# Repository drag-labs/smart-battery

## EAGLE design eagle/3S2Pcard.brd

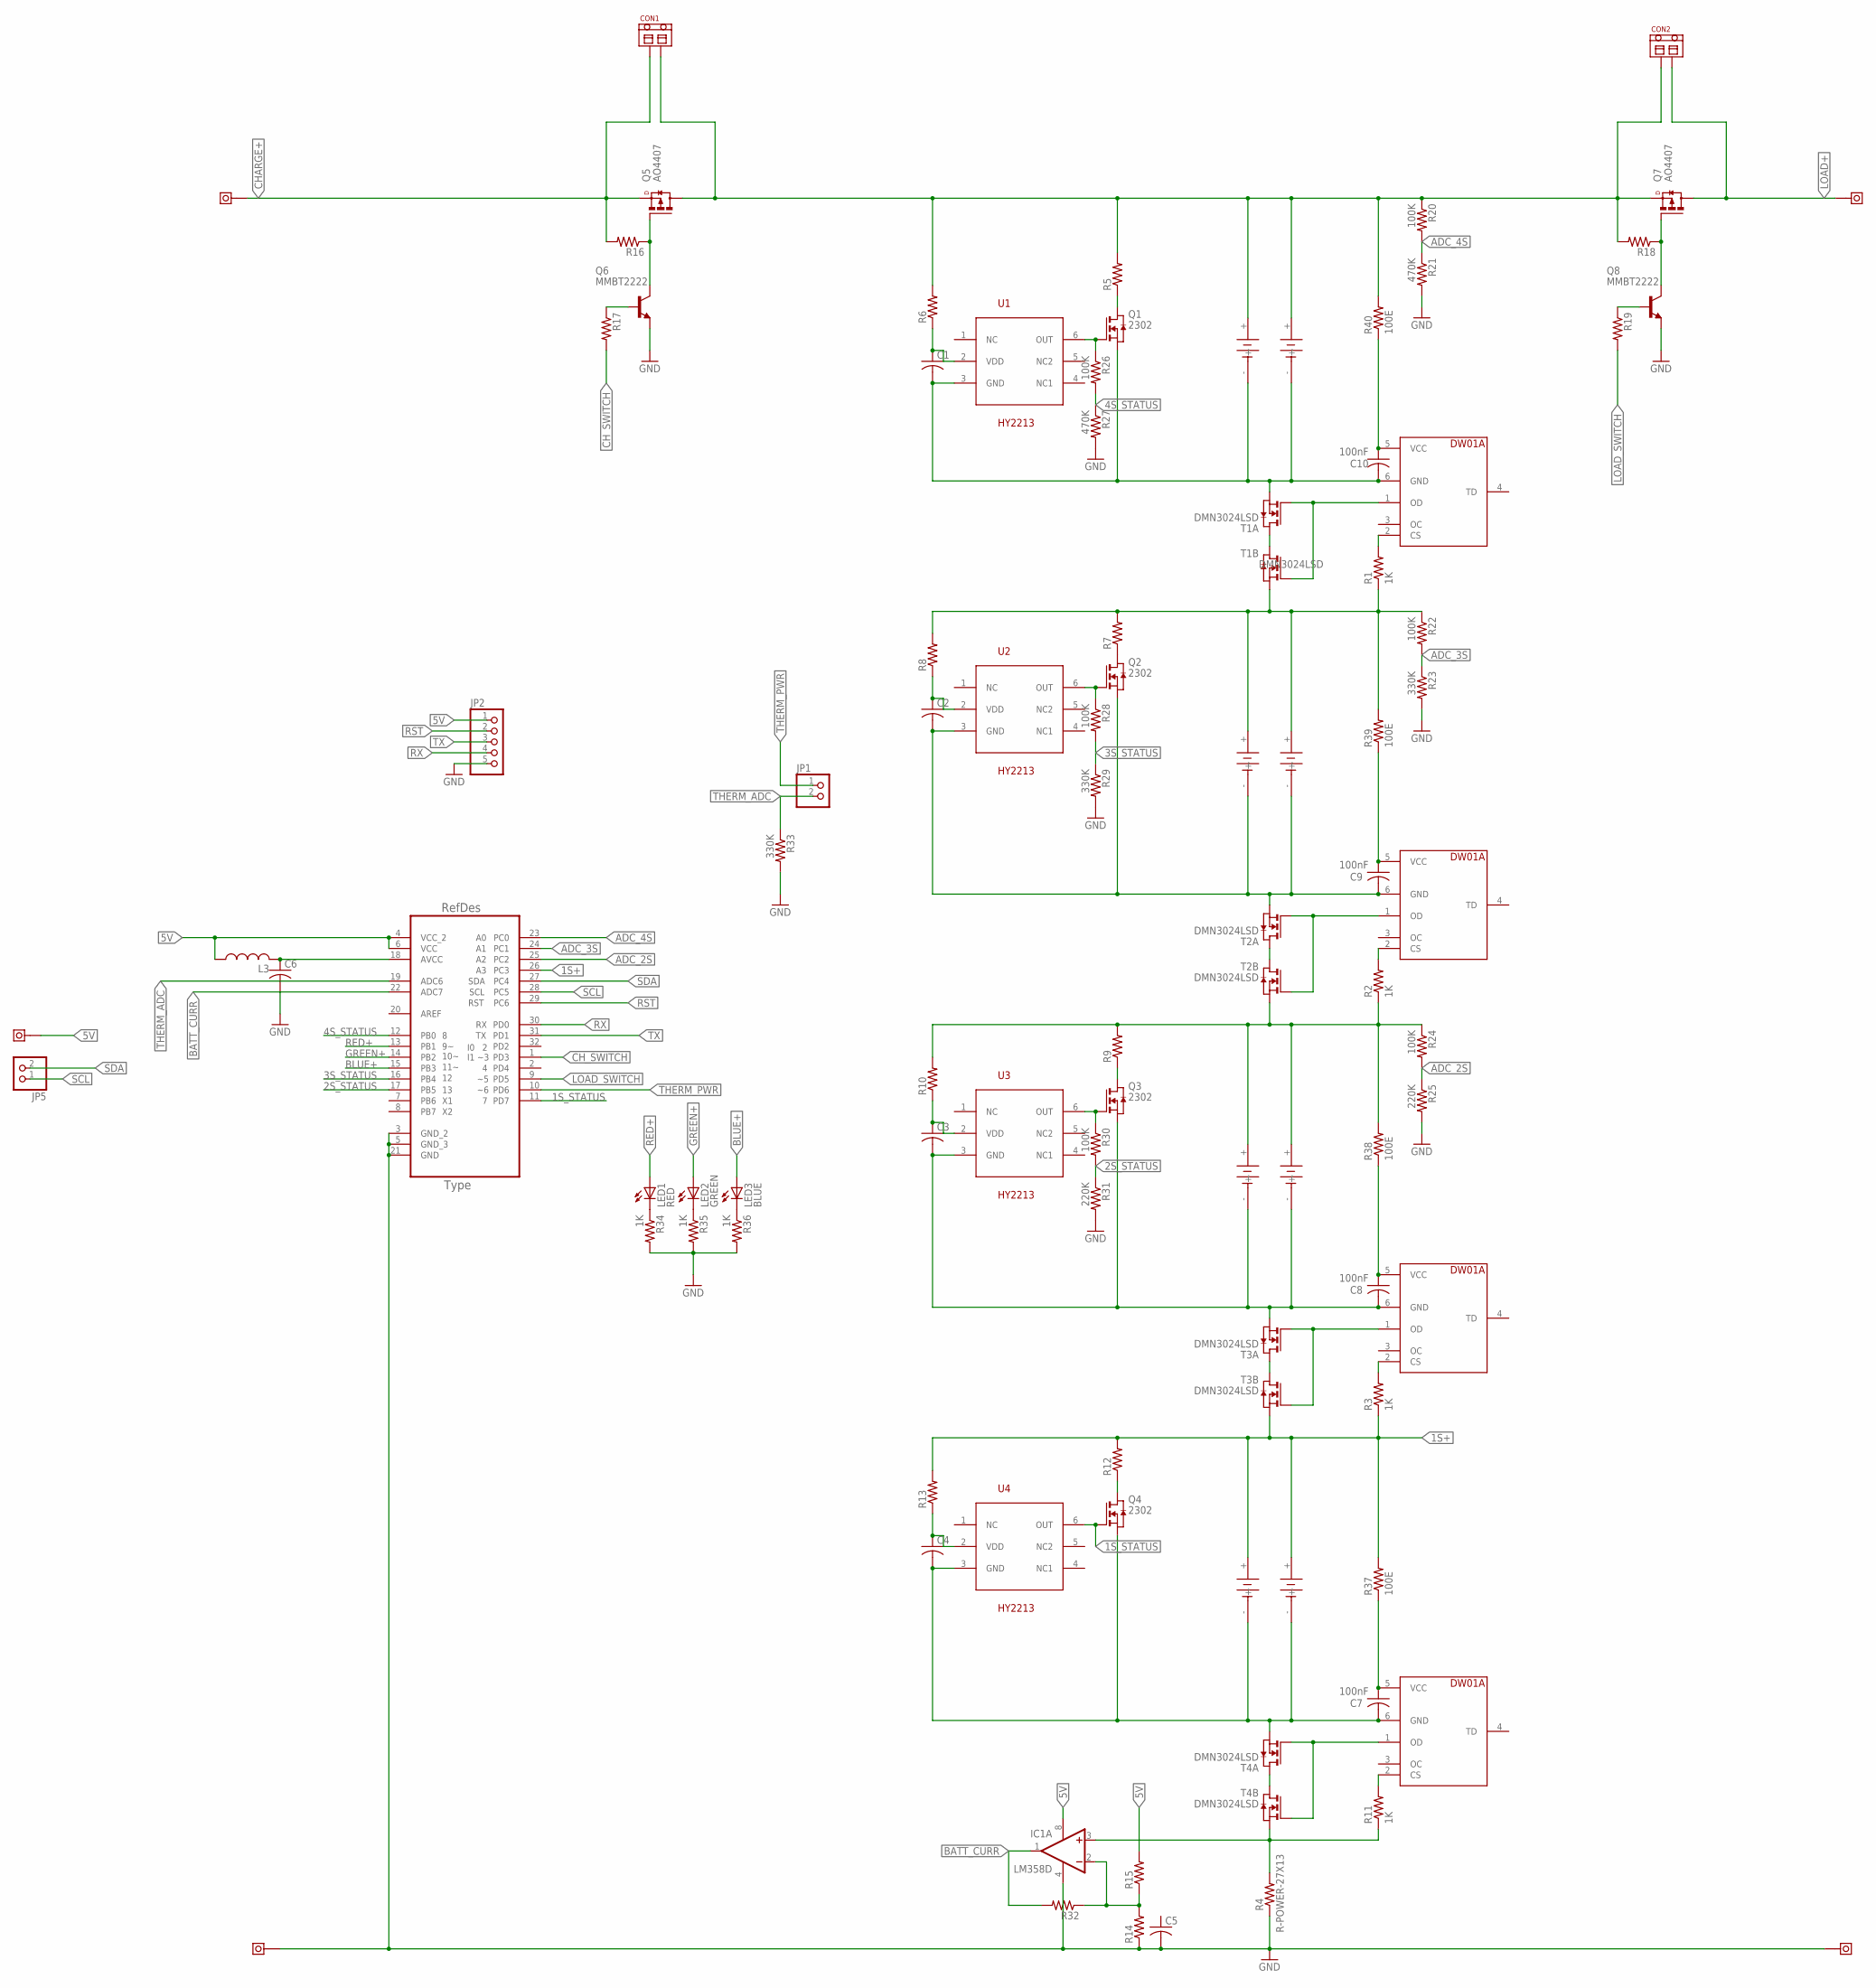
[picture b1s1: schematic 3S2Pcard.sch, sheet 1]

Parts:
B11, B12, B21, B22, B31, B32, B41, B42: 18650_HOLDER
C1, C2, C3, C4, C5, C6: C-USC0805; C0805
C7, C8, C9, C10: 100nF; C0805
CON1, CON2: TERMINAL-SMALL
IC1: LM358D; SO08
JP1, JP5: PINHD-1X2; 1X02
JP2: PINHD-1X5; 1X05
L3: L-US0207/10; 0207/10
LED1: RED; CHIP-LED0805
LED2: GREEN; CHIP-LED0805
LED3: BLUE; CHIP-LED0805
Q1, Q2, Q3, Q4: 2302; TO236
Q5, Q7: AO4407; SOIC8
Q6, Q8: MMBT2222; SOT-23-CBE
R1, R2, R3, R11, R34, R35, R36: 1K; R0805
R4: R-POWER-27X13; R-27X13
R5, R7, R9, R12: R-US_R1206W; R1206W
R6, R8, R10, R13, R14, R15, R16, R17, R18, R19, R32: R-US_R0805; R0805
R20, R22, R24, R26, R28, R30: 100K; R0805
R21, R27: 470K; R0805
R23, R29, R33: 330K; R0805
R25, R31: 220K; R0805
R37, R38, R39, R40: 100E; R0805
T1, T2, T3, T4: DMN3024LSD; TSSOP-8
U1, U2, U3, U4: HY2213; SOT23-6
U5: ATMEGA328P-AU; QFP80P900X900X120-32N
U12: DW01A; SOT23-6
U$7, U$8, U$9: DW01A; SOT23-6
U$13, U$14, U$15, U$16, U$17: METAL_SPACER; SPACER

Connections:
1S+: B11.+, B12.+, R3.1, R12.2, R13.2, R37.2, T3.6 (S), T3.7 (S), U5.26 (PC3)
1S-: B11.-, B12.-, C4.2, C7.2, Q4.3 (S), T4.2 (S), T4.3 (S), U4.3 (GND), U12.6 (GND)
1S_STATUS: Q4.2 (G), U4.6 (OUT), U5.11 (PD7)
2S+: B21.+, B22.+, R2.1, R9.2, R10.2, R24.1, R38.2, T2.6 (S), T2.7 (S)
2S-: B21.-, B22.-, C3.2, C8.2, Q3.3 (S), T3.2 (S), T3.3 (S), U3.3 (GND), U$9.6 (GND)
2S_STATUS: R30.2, R31.1, U5.17 (PB5)
3S+: B31.+, B32.+, R1.1, R7.2, R8.2, R22.1, R39.2, T1.6 (S), T1.7 (S)
3S-: B31.-, B32.-, C2.2, C9.2, Q2.3 (S), T2.2 (S), T2.3 (S), U2.3 (GND), U$8.6 (GND)
3S_STATUS: R28.2, R29.1, U5.16 (PB4)
4S+: B41.+, B42.+, CON1.2, CON2.1, Q5.1 (S), Q5.2 (S), Q5.3 (S), Q7.5 (D), Q7.6 (D), Q7.7 (D), Q7.8 (D), R5.2, R6.2, R18.2, R20.1, R40.2
4S-: B41.-, B42.-, C1.2, C10.2, Q1.3 (S), T1.2 (S), T1.3 (S), U1.3 (GND), U$7.6 (GND)
4S_STATUS: R26.2, R27.1, U5.12 (PB0)
5V: IC1.8 (V+), JP2.1, L3.1, R15.2, U5.4 (VCC_2), U5.6 (VCC), U$17.1
ADC_2S: R24.2, R25.1, U5.25 (PC2)
ADC_3S: R22.2, R23.1, U5.24 (PC1)
ADC_4S: R20.2, R21.1, U5.23 (PC0)
AVCC: C6.1, L3.2, U5.18 (AVCC)
BATT_CURR: IC1.1 (OUT), R32.2, U5.22 (ADC7)
BLUE+: LED3.A, U5.15 (PB3)
CHARGE+: CON1.1, Q5.5 (D), Q5.6 (D), Q5.7 (D), Q5.8 (D), R16.2, U$15.1
CH_SWITCH: R17.2, U5.1 (PD3)
GND: C5.2, C6.2, IC1.4 (V-), JP2.5, Q6.E, Q8.E, R4.1, R14.1, R21.2, R23.2, R25.2, R27.2, R29.2, R31.2, R33.2, R34.2, R35.2, R36.2, U5.3 (GND_2), U5.5 (GND_3), U5.21 (GND), U$14.1, U$16.1
GREEN+: LED2.A, U5.14 (PB2)
LOAD+: CON2.2, Q7.1 (S), Q7.2 (S), Q7.3 (S), U$13.1
LOAD_SWITCH: R19.2, U5.9 (PD5)
unnamed: C7.1, R37.1, U12.5 (VCC)
unnamed: T1.1 (D), T1.8 (D)
unnamed: C8.1, R38.1, U$9.5 (VCC)
unnamed: IC1.2 (-IN), R14.2, R15.1, R32.1
unnamed: T2.1 (D), T2.8 (D)
unnamed: C9.1, R39.1, U$8.5 (VCC)
unnamed: C10.1, R40.1, U$7.5 (VCC)
unnamed: R1.2, U$7.2 (CS)
unnamed: T1.4 (G), T1.5 (G), U$7.1 (OD)
unnamed: R2.2, U$8.2 (CS)
unnamed: T3.1 (D), T3.8 (D)
unnamed: T2.4 (G), T2.5 (G), U$8.1 (OD)
unnamed: LED1.C, R34.1
unnamed: LED2.C, R35.1
unnamed: T3.4 (G), T3.5 (G), U$9.1 (OD)
unnamed: R3.2, U$9.2 (CS)
unnamed: LED3.C, R36.1
unnamed: C1.1, R6.1, U1.2 (VDD)
unnamed: Q1.2 (G), R26.1, U1.6 (OUT)
unnamed: Q1.1 (D), R5.1
unnamed: C2.1, R8.1, U2.2 (VDD)
unnamed: Q2.2 (G), R28.1, U2.6 (OUT)
unnamed: Q2.1 (D), R7.1
unnamed: C3.1, R10.1, U3.2 (VDD)
unnamed: Q3.2 (G), R30.1, U3.6 (OUT)
unnamed: Q3.1 (D), R9.1
unnamed: T4.1 (D), T4.8 (D)
unnamed: T4.4 (G), T4.5 (G), U12.1 (OD)
unnamed: R11.2, U12.2 (CS)
unnamed: C4.1, R13.1, U4.2 (VDD)
unnamed: Q4.1 (D), R12.1
unnamed: IC1.3 (+IN), R4.2, R11.1, T4.6 (S), T4.7 (S)
unnamed: Q5.4 (G), Q6.C, R16.1
unnamed: Q6.B, R17.1
unnamed: Q7.4 (G), Q8.C, R18.1
unnamed: Q8.B, R19.1
RED+: LED1.A, U5.13 (PB1)
RST: JP2.2, U5.29 (PC6)
RX: JP2.4, U5.30 (PD0)
SCL: JP5.1, U5.28 (PC5)
SDA: JP5.2, U5.27 (PC4)
THERM_ADC: JP1.2, R33.1, U5.19 (ADC6)
THERM_PWR: JP1.1, U5.10 (PD6)
TX: JP2.3, U5.31 (PD1)

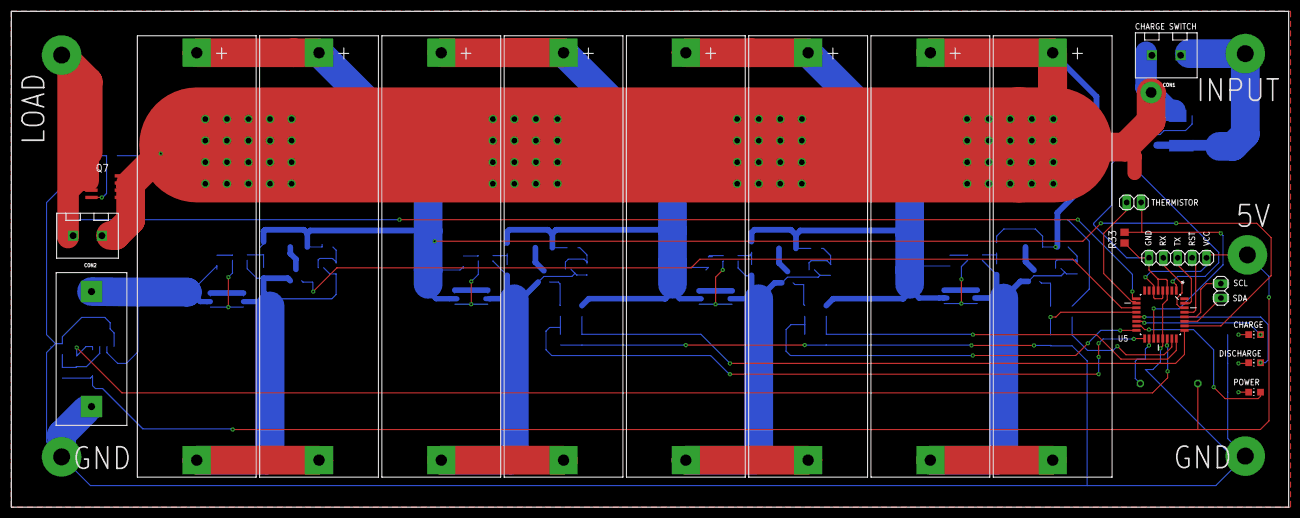
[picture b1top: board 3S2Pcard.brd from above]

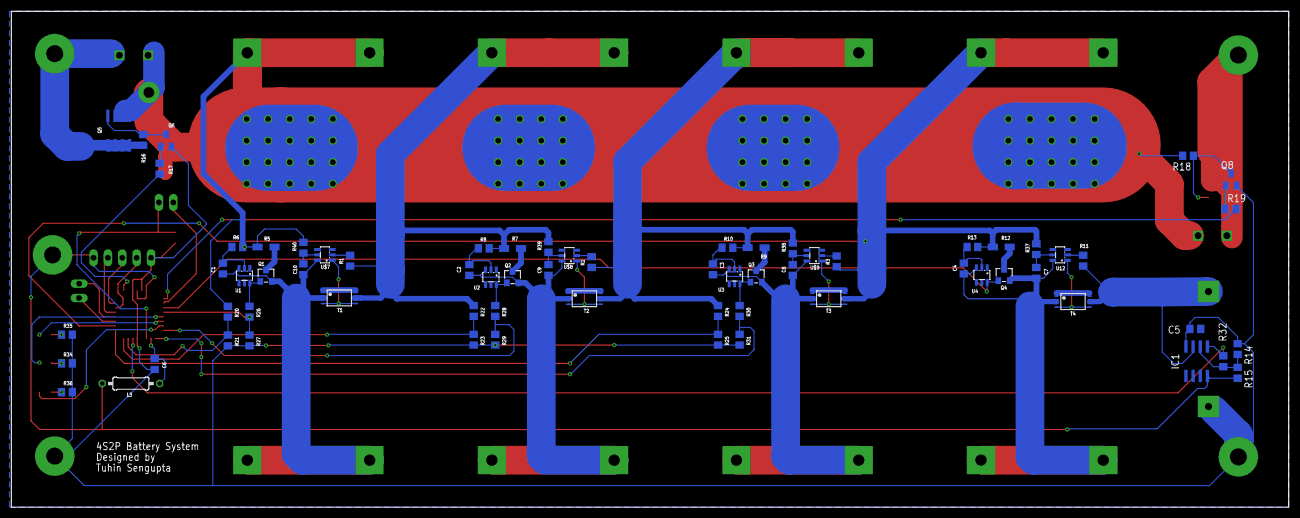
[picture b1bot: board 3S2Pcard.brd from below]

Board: 2 copper layers, 225.7 x 87.6 mm, 94 parts (69 on the bottom side), 69 nets.

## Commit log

2019-11-29 Add: Initial commit, PCB is designedI will have to give for fabrication
